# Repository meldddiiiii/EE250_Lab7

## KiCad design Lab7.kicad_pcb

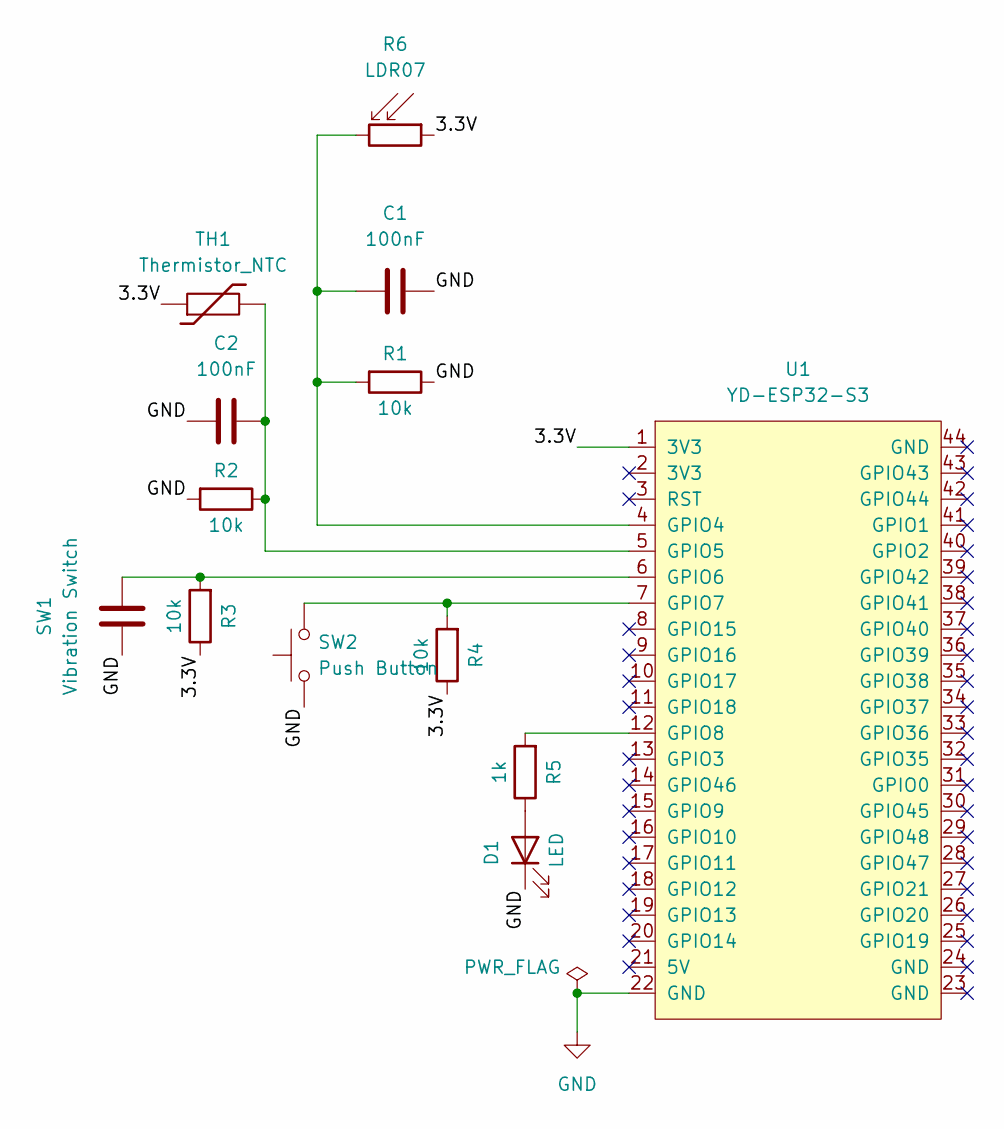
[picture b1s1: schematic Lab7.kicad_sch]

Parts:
C1, C2: 100nF; C_Disc_D5.1mm_W3.2mm_P5.00mm
D1: LED; LED_D5.0mm
R1, R2, R3, R4: 10k; R_Axial_DIN0309_L9.0mm_D3.2mm_P12.70mm_Horizontal
R5: 1k; R_Axial_DIN0309_L9.0mm_D3.2mm_P12.70mm_Horizontal
R6: LDR07; R_LDR_5.1x4.3mm_P3.4mm_Vertical
SW1: Vibration Switch; CP_Radial_D5.0mm_P2.50mm
SW2: Push Button; SW_PUSH_6mm_2pin
TH1: Thermistor_NTC; CP_Radial_D5.0mm_P2.50mm
U1: YD-ESP32-S3

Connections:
/3.3V: R3.1, R4.1, R6.1, TH1.1, U1.1 (3V3)
GND: C1.2, C2.1, D1.1 (K), R1.1, R2.2, SW1.1, SW2.1, U1.22 (GND)
unnamed: D1.2 (A), R5.1
unnamed: C1.1, R1.2, R6.2, U1.4 (GPIO4)
unnamed: C2.2, R2.1, TH1.2, U1.5 (GPIO5)
unnamed: R3.2, SW1.2, U1.6 (GPIO6)
unnamed: R4.2, SW2.2, U1.7 (GPIO7)
unnamed: R5.2, U1.12 (GPIO8)

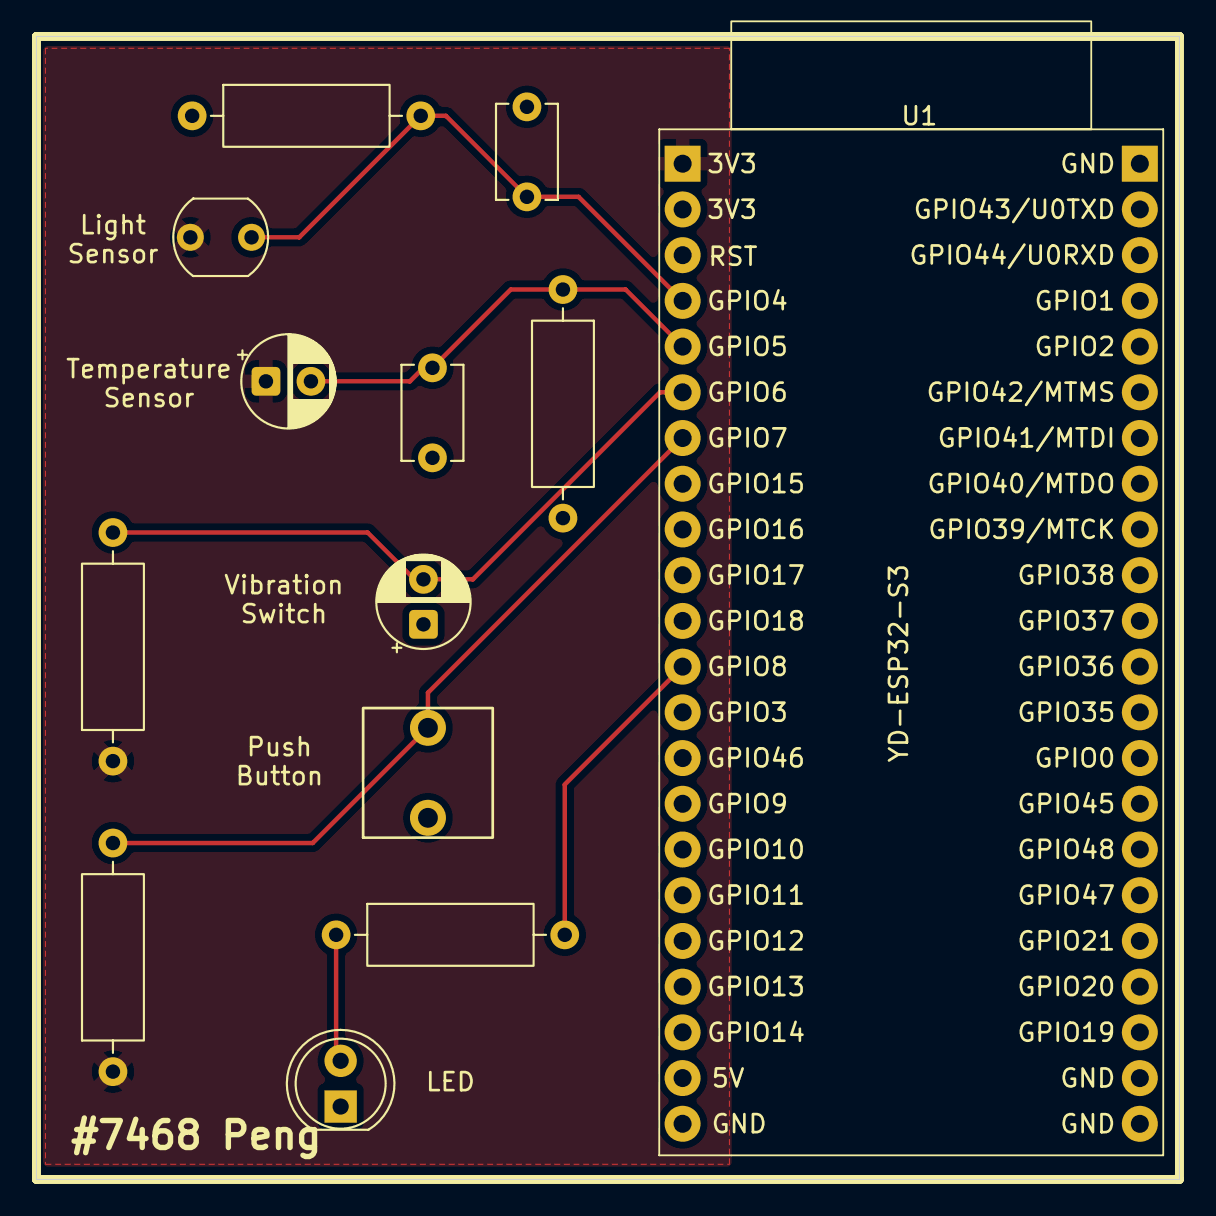
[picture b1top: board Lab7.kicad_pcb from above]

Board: 2 copper layers, 63.5 x 63.5 mm, 13 parts (0 on the bottom side), 8 nets.
